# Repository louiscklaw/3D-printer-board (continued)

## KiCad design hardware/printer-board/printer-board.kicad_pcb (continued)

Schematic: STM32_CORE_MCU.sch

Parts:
C21, C23, C25, C26, C27, C28, C30, C31, C32: C104,0603; C_0603_1608Metric_Pad1.05x0.95mm_HandSolder
C22, C24: C10pf,0603; C_0603_1608Metric_Pad1.05x0.95mm_HandSolder
C29, C55: C105,0603; C_0603_1608Metric_Pad1.05x0.95mm_HandSolder
D17: PB9; LED_0603_1608Metric_Pad1.05x0.95mm_HandSolder
J28: SWD; PinHeader_1x04_P2.54mm_Vertical
J29: USB_DBG; PinHeader_1x05_P1.27mm_Vertical
J43: STM32_GTR; PinHeader_1x03_P1.27mm_Vertical
J44: SPI_DBG; PinHeader_1x04_P1.27mm_Vertical
JP6: BOOT0; SolderJumper-2_P1.3mm_Open_TrianglePad1.0x1.5mm
JP7: BOOT1; SolderJumper-2_P1.3mm_Open_TrianglePad1.0x1.5mm
JP10: RST; SW_SPST_CK_RS282G05A3
L1: L_2R2,1210; L_1210_3225Metric_Pad1.42x2.65mm_HandSolder
R3, R47: R220,0603; R_0603_1608Metric_Pad1.05x0.95mm_HandSolder
R40, R41: R472,0603; R_0603_1608Metric_Pad1.05x0.95mm_HandSolder
R42: R0,0603; C_0603_1608Metric_Pad1.05x0.95mm_HandSolder
R43: R0,0603; R_0603_1608Metric_Pad1.05x0.95mm_HandSolder
R44: R102,0603; R_0805_2012Metric_Pad1.15x1.40mm_HandSolder
R45, R46: R103,0603; R_0603_1608Metric_Pad1.05x0.95mm_HandSolder
R48: R152,0603; R_0603_1608Metric_Pad1.05x0.95mm_HandSolder
U8: STM32F407VET6; TQFP-100
Y1: O_8M,3225; OSC_3225

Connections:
/STM32_CORE/STM32_CORE_MCU/BOOT0: JP6.2, R46.1, U8.94 (BOOT0)
/STM32_CORE/STM32_CORE_MCU/BOOT1: JP7.2, R45.1, U8.37 (PB2/BOOT1)
/STM32_CORE/STM32_CORE_MCU/DM: R3.1, U8.70 (PA11/D-)
/STM32_CORE/STM32_CORE_MCU/DP: R47.1, R48.1, U8.71 (PA12/D+)
/STM32_CORE/STM32_CORE_MCU/GND-CAP1: C30.1, U8.49 (VSS_1/VCAP_1)
/STM32_CORE/STM32_CORE_MCU/GND-CAP2: C31.1, U8.73 (NC/VCAP_2)
/STM32_CORE/STM32_CORE_MCU/GND-VCC3V3: R42.1, R43.1, U8.19 (VSSA/VDD)
/STM32_CORE/STM32_CORE_MCU/MISO2: J44.2, U8.53 (PB14/MISO2)
/STM32_CORE/STM32_CORE_MCU/MOSI2: J44.1, U8.54 (PBI5/MOSI2)
/STM32_CORE/STM32_CORE_MCU/PB9: R44.1, U8.96 (PB9)
/STM32_CORE/STM32_CORE_MCU/RESET: C32.1, JP10.1 (A), U8.14 (NRST)
/STM32_CORE/STM32_CORE_MCU/SCK: J44.3, U8.52 (PB13/SCK2)
/STM32_CORE/STM32_CORE_MCU/SWCLK: J28.2, U8.76 (PA14/JTCK/SWCLK)
/STM32_CORE/STM32_CORE_MCU/SWDIO: J28.3, U8.72 (PA13/JTMS/SWDIO)
/STM32_CORE/STM32_SCL1: U8.92 (PB6/SCL1)
/STM32_CORE/STM32_SDA1: U8.93 (PB7/SDA1)
/orange_pi/OPI_USB-DM2: J29.2, R3.2; also elsewhere on the board
/orange_pi/OPI_USB-DP2: J29.3, R47.2; also elsewhere on the board
GND: C21.2, C22.2, C23.2, C24.2, C25.1, C26.1, C27.1, C28.1, C29.1, C30.2, C31.2, C32.2, C55.1, J28.1, J29.4, J29.5, J43.3, J44.4, JP10.2 (B), R43.2, R45.2, R46.2, U8.10 (VSS_5), U8.20 (VREF-), U8.27 (VSS_4), U8.74 (VSS_2), U8.99 (VSS_3), Y1.2; also elsewhere on the board
unnamed: C21.1, L1.2, U8.21 (VREF+)
unnamed: C22.1, U8.12 (OSC_IN), Y1.1
unnamed: C23.1, U8.6 (VBAT)
unnamed: C24.1, U8.13 (OSC_OUT), Y1.3
unnamed: D17.1 (K), R44.2
unnamed: J43.1, U8.69 (PA10/RX1)
unnamed: J43.2, U8.68 (PA9/TX1)
unnamed: JP6.1, R40.1
unnamed: JP7.1, R41.1
PA0: U8.23 (PA0/WKUP/ADC0); also elsewhere on the board
PA1: U8.24 (PA1/ADC1); also elsewhere on the board
PA2: U8.25 (PA2/ADC2/TX2); also elsewhere on the board
PA3: U8.26 (PA3/ADC3/RX2); also elsewhere on the board
PA4: U8.29 (PA4/ADC4/NSS1); also elsewhere on the board
PA6: U8.31 (PA6/ADC6/MISO1); also elsewhere on the board
PA7: U8.32 (PA7/ADC7/MOSI1); also elsewhere on the board
PA8: U8.67 (PA8/MCO); also elsewhere on the board
PA15: U8.77 (PA15/JTDI); also elsewhere on the board
PB5: U8.91 (PB5); also elsewhere on the board
PC0: U8.15 (PCO/ADC10); also elsewhere on the board
PC1: U8.16 (PC1/ADC11); also elsewhere on the board
PC2: U8.17 (PC2/ADC12); also elsewhere on the board
PC3: U8.18 (PC3/ADC13); also elsewhere on the board
PC4: U8.33 (PC4/ADC14); also elsewhere on the board
PC6: U8.63 (PC6); also elsewhere on the board
PC10: U8.78 (PC10); also elsewhere on the board
PC11: U8.79 (PC11); also elsewhere on the board
PC12: U8.80 (PC12); also elsewhere on the board
PC13: U8.7 (PC13/TAMP/RTC); also elsewhere on the board
PC14: U8.8 (PC14/OSCIN); also elsewhere on the board
PC15: U8.9 (PC15/OSCOUT); also elsewhere on the board
PD0: U8.81 (PD0); also elsewhere on the board
PD1: U8.82 (PD1); also elsewhere on the board
PD2: U8.83 (PD2); also elsewhere on the board
PD3: U8.84 (PD3); also elsewhere on the board
PD4: U8.85 (PD4); also elsewhere on the board
PD5: U8.86 (PD5); also elsewhere on the board
PD6: U8.87 (PD6); also elsewhere on the board
PD7: U8.88 (PD7); also elsewhere on the board
PD13: U8.60 (PD13); also elsewhere on the board
PD14: U8.61 (Pd14); also elsewhere on the board
PD15: U8.62 (PD15); also elsewhere on the board
PE2: U8.1 (PE2); also elsewhere on the board
PE3: U8.2 (PE3); also elsewhere on the board
PE4: U8.3 (PE4); also elsewhere on the board
PE7: U8.38 (PE7); also elsewhere on the board
PE8: U8.39 (PE8); also elsewhere on the board
PE9: U8.40 (PE9); also elsewhere on the board
PE10: U8.41 (PE10); also elsewhere on the board
PE11: U8.42 (PE11); also elsewhere on the board
PE12: U8.43 (PE12); also elsewhere on the board
PE13: U8.44 (PE13); also elsewhere on the board
PE14: U8.45 (PE14); also elsewhere on the board
PE15: U8.46 (PE15); also elsewhere on the board

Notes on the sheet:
When using USB, the PA11 (D-) and PA12 (D+) pins are reserved. The USB code assumes that PA12 (D+) has a fixed pullup resistor attached to it.
THIS IS OPTIONAL REFER TO OPi side
General considerations: The STM32 port currently requires an 8 MHz crystal for correct operation General considerations: When using serial, the UART used for communication with the host is fixed to pins PA9 (TX) and PA10 (RX). When using USB, the PA11 (D-) and PA12 (D+) pins are reserved. The USB c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

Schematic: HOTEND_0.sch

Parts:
D18: LED_RED,0603; LED_0603_1608Metric_Pad1.05x0.95mm_HandSolder
J31: HOT_END; mpt_0,5%2f2-2,54,heatbed
Q2: STP55NF06; TO-263-2,thermal_vias
R50: R100,0805; R_0805_2012Metric_Pad1.15x1.40mm_HandSolder
R51: R104,0805; R_0805_2012Metric_Pad1.15x1.40mm_HandSolder
R52: R182,0603; R_0603_1608Metric_Pad1.05x0.95mm_HandSolder

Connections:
+12V: J31.1, R52.2; also elsewhere on the board
/HOTENDS/HOTEND_0/-12V: D18.1 (K), J31.2, Q2.2 (D)
GND: Q2.3 (S), R51.1; also elsewhere on the board
unnamed: D18.2 (A), R52.1
unnamed: Q2.1 (G), R50.1
unnamed 152: R50.2, R51.2; also elsewhere on the board

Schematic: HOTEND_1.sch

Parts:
D19: LED_RED,0603; LED_0603_1608Metric_Pad1.05x0.95mm_HandSolder
J32: HOT_END; mpt_0,5%2f2-2,54,heatbed
Q3: STP55NF06; TO-263-2,thermal_vias
R53: R100,0805; R_0805_2012Metric_Pad1.15x1.40mm_HandSolder
R54: R104,0805; R_0805_2012Metric_Pad1.15x1.40mm_HandSolder
R55: R182,0603; R_0603_1608Metric_Pad1.05x0.95mm_HandSolder

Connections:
+12V: J32.1, R55.2; also elsewhere on the board
/HOTENDS/HOTEND_1/-12V: D19.1 (K), J32.2, Q3.2 (D)
GND: Q3.3 (S), R54.1; also elsewhere on the board
unnamed: D19.2 (A), R55.1
unnamed: Q3.1 (G), R53.1
unnamed 154: R53.2, R54.2; also elsewhere on the board

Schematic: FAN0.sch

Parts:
C36: CP1uf,50V; CP_Elec_4x5.3
D20: LED_BLUE,0603; LED_0603_1608Metric_Pad1.05x0.95mm_HandSolder
J33: TO FAN0; b2b-ph-kl,fan_pwm_out
Q4: D882; SOT-89-3,thermal_vias
R56: R100,0805; R_0805_2012Metric_Pad1.15x1.40mm_HandSolder
R57: R104,0805; R_0805_2012Metric_Pad1.15x1.40mm_HandSolder
R58: R100,0603; R_0603_1608Metric_Pad1.05x0.95mm_HandSolder
R59: R182,0603; R_0603_1608Metric_Pad1.05x0.95mm_HandSolder

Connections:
+12V: C36.1, J33.1, R59.2; also elsewhere on the board
/FANS/FAN0/FAN0_N: C36.2, D20.1 (K), J33.2, R58.1
GND: Q4.3 (E), R57.1; also elsewhere on the board
unnamed: D20.2 (A), R59.1
unnamed: Q4.1 (B), R56.1
unnamed: Q4.2 (C), R58.2
PA6: R56.2, R57.2; also elsewhere on the board

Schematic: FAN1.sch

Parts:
C37: CP1uf,50V; CP_Elec_4x5.3
D21: LED_BLUE,0603; LED_0603_1608Metric_Pad1.05x0.95mm_HandSolder
J34: TO FAN1; b2b-ph-kl,fan_pwm_out
Q5: D882; SOT-89-3,thermal_vias
R60: R100,0805; R_0805_2012Metric_Pad1.15x1.40mm_HandSolder
R61: R104,0805; R_0805_2012Metric_Pad1.15x1.40mm_HandSolder
R62: R100,0603; R_0603_1608Metric_Pad1.05x0.95mm_HandSolder
R63: R182,0603; R_0603_1608Metric_Pad1.05x0.95mm_HandSolder

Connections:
+12V: C37.1, J34.1, R63.2; also elsewhere on the board
/FANS/FAN1/FAN1_N: C37.2, D21.1 (K), J34.2, R62.1
GND: Q5.3 (E), R61.1; also elsewhere on the board
unnamed: D21.2 (A), R63.1
unnamed: Q5.1 (B), R60.1
unnamed: Q5.2 (C), R62.2
PA7: R60.2, R61.2; also elsewhere on the board

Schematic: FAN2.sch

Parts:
C38: CP1uf,50V; CP_Elec_4x5.3
D22: LED_BLUE,0603; LED_0603_1608Metric_Pad1.05x0.95mm_HandSolder
J35: TO FAN2; b2b-ph-kl,fan_pwm_out
Q6: D882; SOT-89-3,thermal_vias
R64: R100,0805; R_0603_1608Metric_Pad1.05x0.95mm_HandSolder
R65: R104,0805; R_0805_2012Metric_Pad1.15x1.40mm_HandSolder
R66: R100,0603; R_0603_1608Metric_Pad1.05x0.95mm_HandSolder
R67: R182,0603; R_0603_1608Metric_Pad1.05x0.95mm_HandSolder

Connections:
+12V: C38.1, J35.1, R67.2; also elsewhere on the board
/FANS/FAN2/FAN2_N: C38.2, D22.1 (K), J35.2, R66.1
GND: Q6.3 (E), R65.1; also elsewhere on the board
unnamed: D22.2 (A), R67.1
unnamed: Q6.1 (B), R64.1
unnamed: Q6.2 (C), R66.2
PA8: R64.2, R65.2; also elsewhere on the board

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
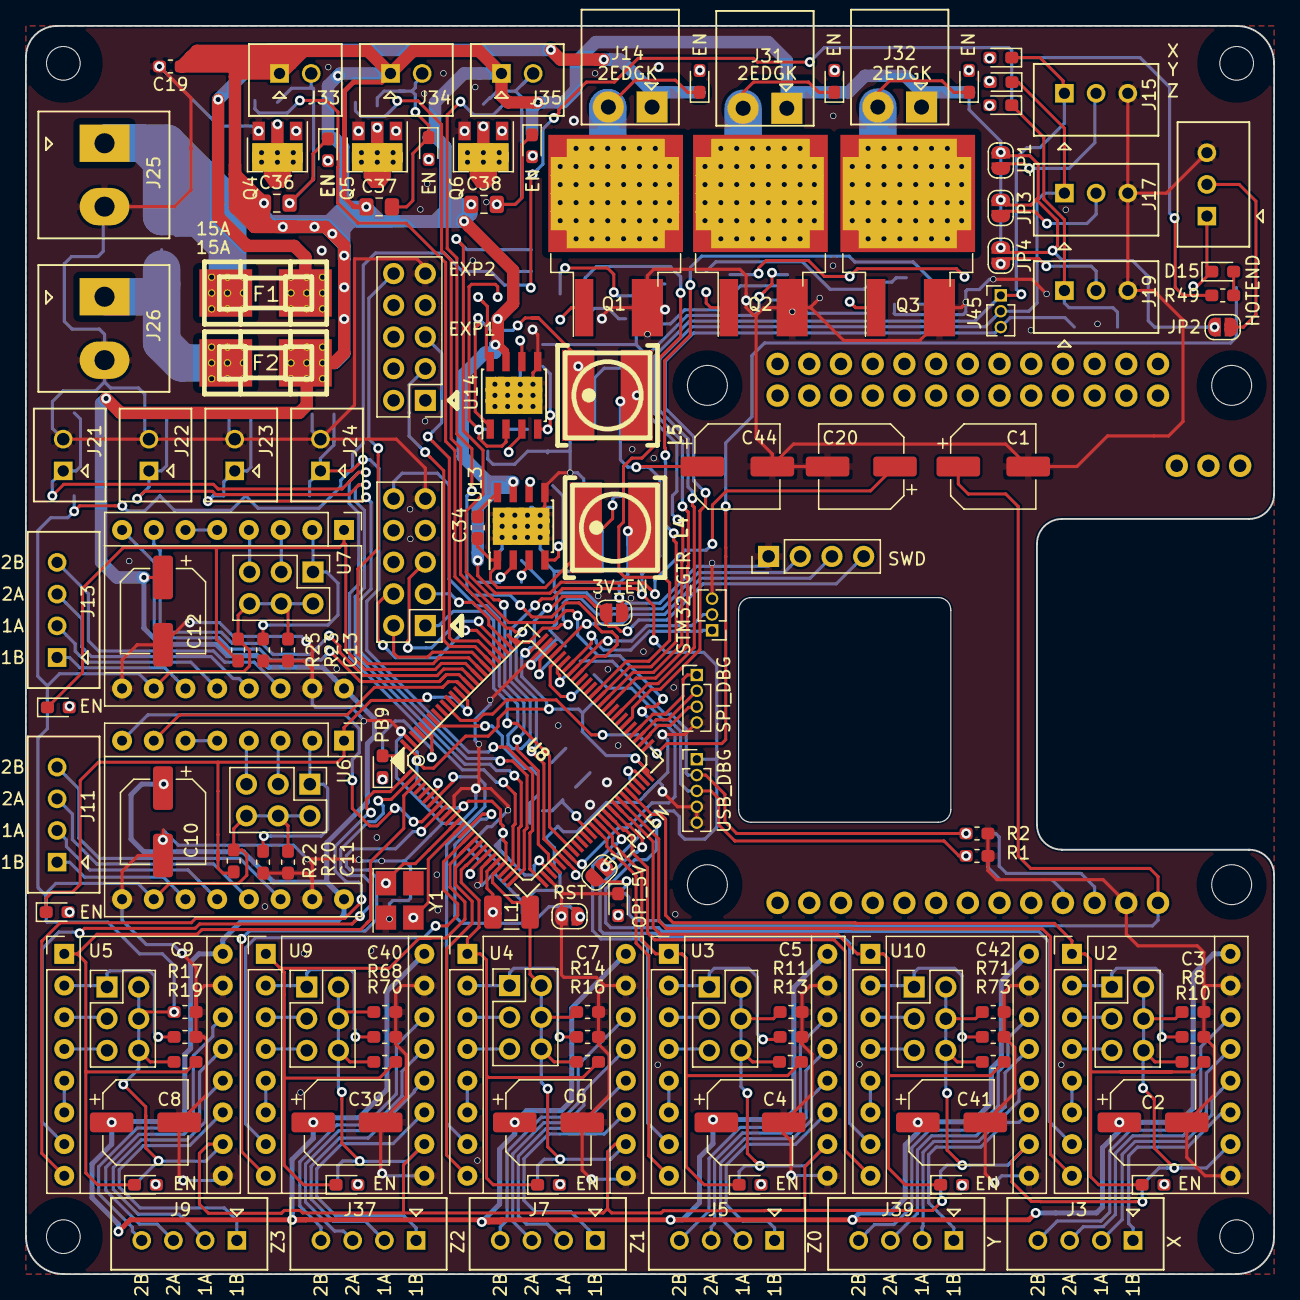
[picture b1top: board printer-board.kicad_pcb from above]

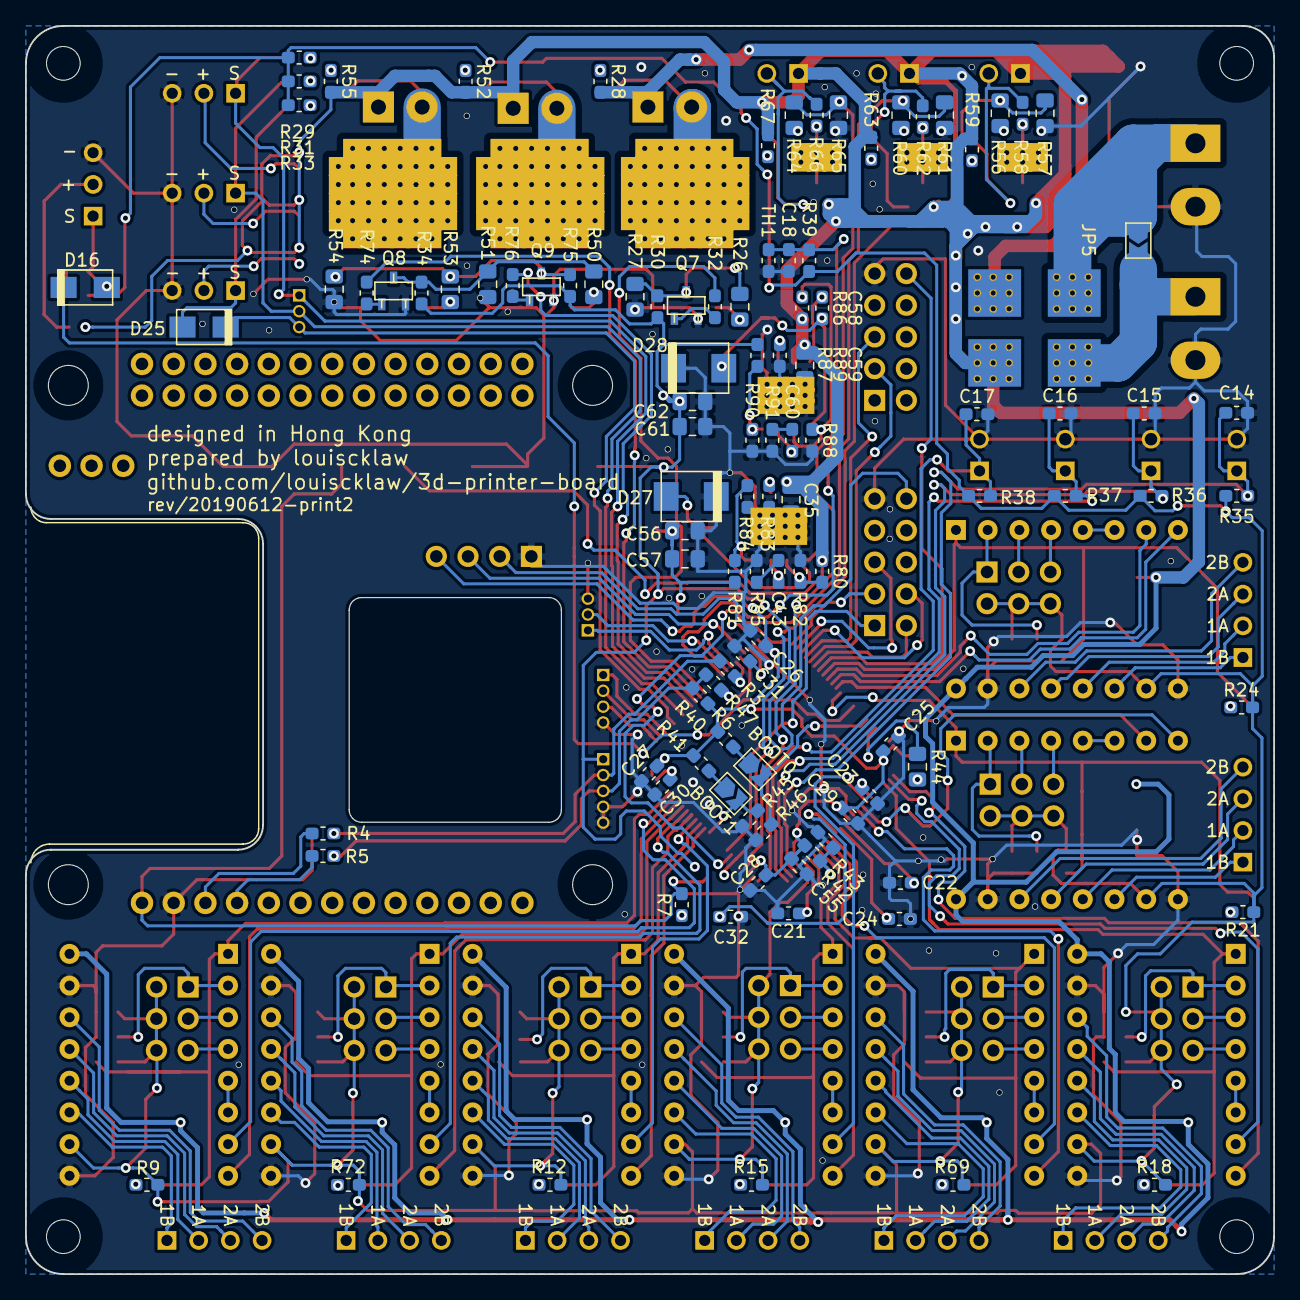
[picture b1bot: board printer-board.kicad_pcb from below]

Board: 2 copper layers, 100.0 x 100.0 mm, 243 parts (107 on the bottom side), 207 nets.

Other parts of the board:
C58: C104,0603; C_0603_1608Metric_Pad1.05x0.95mm_HandSolder
C59, C61, C62: C106,0805; C_0805_2012Metric_Pad1.15x1.40mm_HandSolder
C60: C151,0603; C_0603_1608Metric_Pad1.05x0.95mm_HandSolder
D28: SD_1N5822_SS34; do214aa
JP3, JP4: 12V_EN; SolderJumper-2_P1.3mm_Open_RoundedPad1.0x1.5mm
L5: L_15uH; inductor_smd_6.8x3.8mm
Q7, Q8, Q9: SS9013_J3; 9013,J3,SOT23
R74, R76: R471,0603; R_0603_1608Metric_Pad1.05x0.95mm_HandSolder
R75: R331,0603; R_0603_1608Metric_Pad1.05x0.95mm_HandSolder
R86, R89, R91: R104,0603; R_0603_1608Metric_Pad1.05x0.95mm_HandSolder
R87: R224,0603; R_0603_1608Metric_Pad1.05x0.95mm_HandSolder
R88: R240,0603; R_0603_1608Metric_Pad1.05x0.95mm_HandSolder
R90: R433,0603; R_0603_1608Metric_Pad1.05x0.95mm_HandSolder
U14: MP1584; MP1584,SOIC-8_3.9x4.9mm_P1.27mm,thermal_via

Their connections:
+12V: C59.1, JP3.1, JP4.1, R86.1, U14.7; also elsewhere on the board
GND: C59.2, C61.2, C62.2, D28.2, Q7.2, Q8.2, Q9.2, R88.2, R89.2, R90.2, R91.2, U14.5, U14.G; also elsewhere on the board
unnamed: C58.1, D28.1, L5.1, U14.1
unnamed: C58.2, U14.8
unnamed: C60.1, U14.3
unnamed: C60.2, R91.1
unnamed 150: Q7.3; also elsewhere on the board
unnamed: Q8.1, R74.1
unnamed 152: Q8.3; also elsewhere on the board
unnamed: Q9.1, R76.1
unnamed 154: Q9.3, R75.2; also elsewhere on the board
unnamed: R86.2, R88.1, U14.2
unnamed: R87.2, R90.1, U14.4
unnamed: R89.1, U14.6
PD14: R76.2; also elsewhere on the board
PD15: R74.2; also elsewhere on the board

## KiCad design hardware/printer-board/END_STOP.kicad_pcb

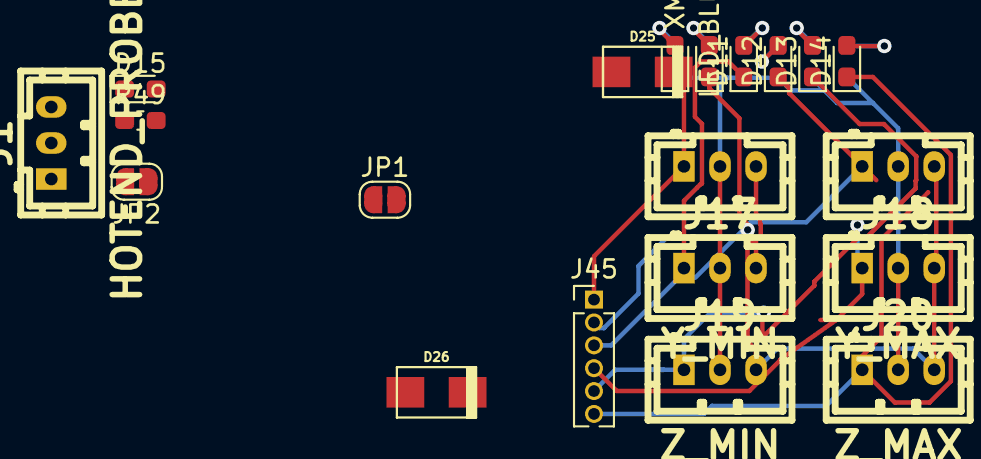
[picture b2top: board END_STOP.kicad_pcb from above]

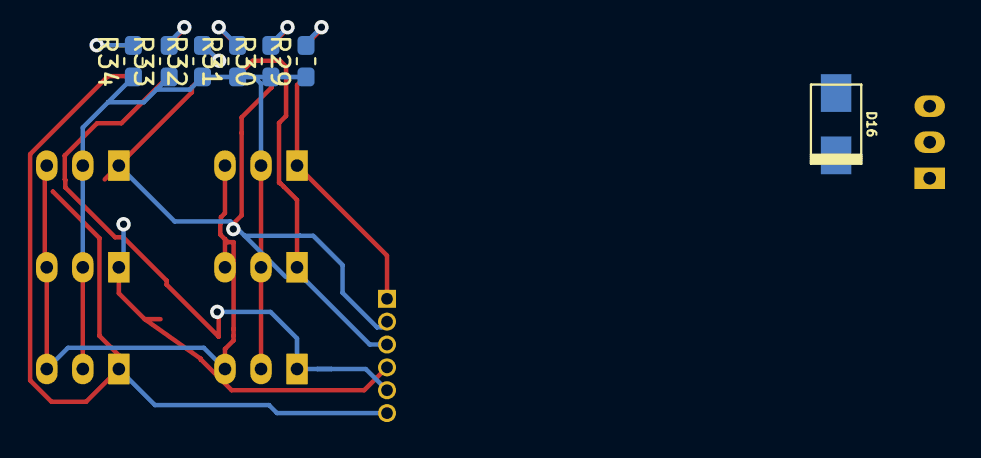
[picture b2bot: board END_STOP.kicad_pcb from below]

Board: 2 copper layers, 27 parts (7 on the bottom side), 21 nets.

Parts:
D9: XMIN; LED_0603_1608Metric_Pad1.05x0.95mm_HandSolder
D10, D11, D12, D13, D14, D15: LED_BLUE,0603; LED_0603_1608Metric_Pad1.05x0.95mm_HandSolder
D16, D25, D26: SD_1N5817_SS12; do214ac
J1: HOTEND_PROBE; b3b-ph-kl,end_stop
J15: X_MIN; b3b-ph-kl,end_stop
J16: X_MAX; b3b-ph-kl,end_stop
J17: Y_MIN; b3b-ph-kl,end_stop
J18: Y_MAX; b3b-ph-kl,end_stop
J19: Z_MIN; b3b-ph-kl,end_stop
J20: Z_MAX; b3b-ph-kl,end_stop
J45: END_SWITCH_DEBUG; PinHeader_1x06_P1.27mm_Vertical
JP1, JP2: SolderJumper_2_Open; SolderJumper-2_P1.3mm_Open_RoundedPad1.0x1.5mm
R29, R30, R31, R32, R33, R34, R49: R102,0603; R_0603_1608Metric_Pad1.05x0.95mm_HandSolder

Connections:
+3V3_STM32: R29.1, R30.1, R31.1, R32.1, R33.1, R34.1, R49.1
+12V: JP1.1, JP2.1
/X_MAX: D10.1, J16.1, J45.2
/X_MIN: D9.1, J15.1, J45.1
/Y_MAX: D12.1, J18.1, J45.4
/Y_MIN: D11.1, J17.1, J45.3
/Z_MAX: D26.2, J45.6
/Z_MIN: D25.2, J45.5
GND: J1.3, J15.3, J16.3, J17.3, J18.3, J19.3, J20.3
unnamed: D9.2, R29.2
unnamed: D10.2, R30.2
unnamed: D11.2, R31.2
unnamed: D12.2, R32.2
unnamed: D13.1, D25.1, J19.1
unnamed: D13.2, R33.2
unnamed: D14.1, D26.1, J20.1
unnamed: D14.2, R34.2
unnamed: D15.1, D16.1, J1.1
unnamed: D15.2, R49.2
unnamed: J1.2, JP2.2
unnamed: J15.2, J16.2, J17.2, J18.2, J19.2, J20.2, JP1.2

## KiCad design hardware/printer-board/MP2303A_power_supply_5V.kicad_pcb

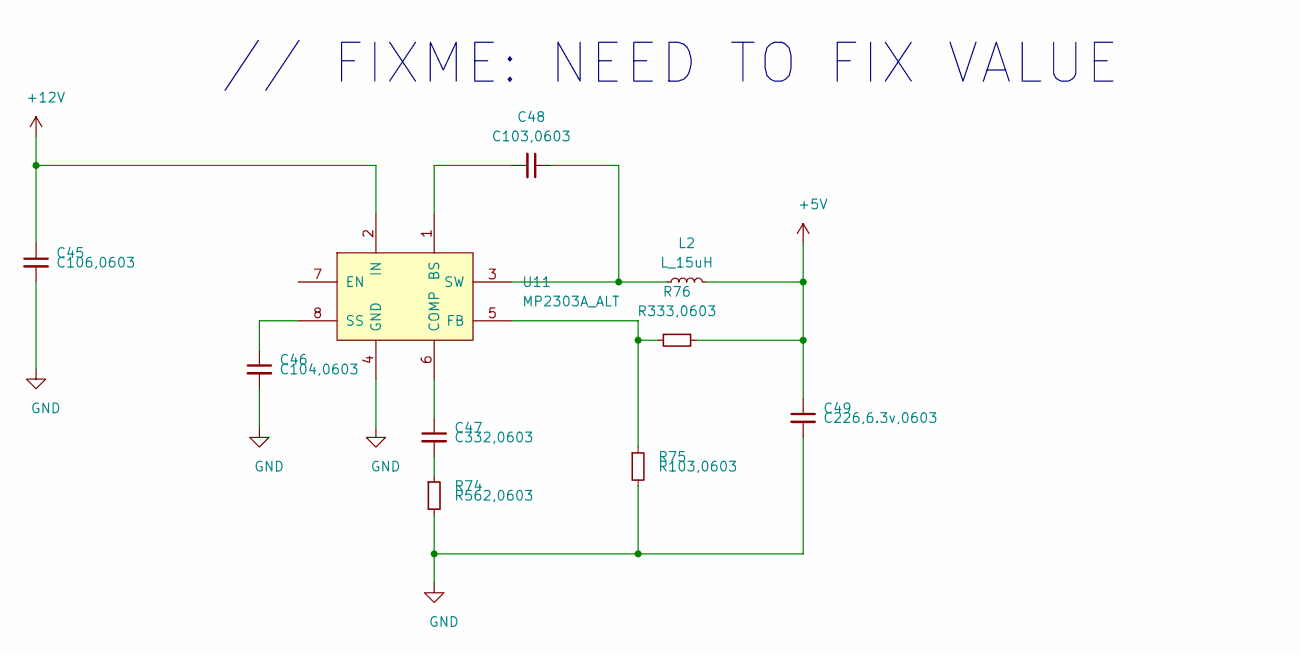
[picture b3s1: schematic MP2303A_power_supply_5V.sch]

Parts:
C45: C106,0603; C_0603_1608Metric_Pad1.05x0.95mm_HandSolder
C46: C104,0603; C_0603_1608Metric_Pad1.05x0.95mm_HandSolder
C47: C332,0603; C_0603_1608Metric_Pad1.05x0.95mm_HandSolder
C48: C103,0603; C_0603_1608Metric_Pad1.05x0.95mm_HandSolder
C49: C226,6.3v,0603; C_0603_1608Metric_Pad1.05x0.95mm_HandSolder
L2: L_15uH; inductor_smd_4.8x2.8mm
R74: R562,0603; R_0603_1608Metric_Pad1.05x0.95mm_HandSolder
R75: R103,0603; R_0603_1608Metric_Pad1.05x0.95mm_HandSolder
R76: R333,0603; R_0603_1608Metric_Pad1.05x0.95mm_HandSolder
U11: MP2303A_ALT; SOIC-8_3.9x4.9mm_P1.27mm,thermal_via

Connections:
+5V: C49.1, L2.2, R76.1
+12V: C45.1, U11.2 (IN)
GND: C45.2, C46.2, C49.2, R74.2, R75.2, U11.4 (GND)
unnamed: C46.1, U11.8 (SS)
unnamed: C47.1, U11.6 (COMP)
unnamed: C47.2, R74.1
unnamed: C48.1, L2.1, U11.3 (SW)
unnamed: C48.2, U11.1 (BS)
unnamed: R75.1, R76.2, U11.5 (FB)

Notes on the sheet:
// FIXME: NEED TO FIX VALUE

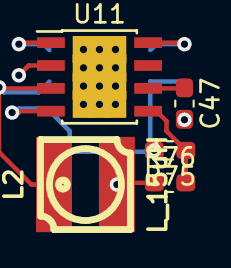
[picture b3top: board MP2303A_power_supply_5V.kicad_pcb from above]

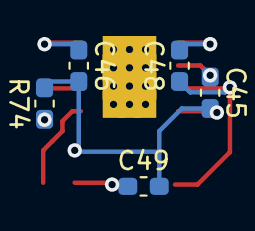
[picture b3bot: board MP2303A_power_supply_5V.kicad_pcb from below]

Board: 2 copper layers, 10 parts (5 on the bottom side), 9 nets.

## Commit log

2019-04-01 update,
2019-04-26 update to add indicator for end-stop,
2019-04-26 update design goal,
2019-04-27 update for endstop circuit,
2019-04-27 update to reverse NO/NC,
2019-04-27 update for stepper motor circuit,
2019-04-27 update to remove E3,
2019-04-27 udpate design goal,
2019-04-27 update label,
2019-04-27 update power supply circuit,
2019-04-27 update hotend MOSFET,
2019-04-27 update power tree,
2019-04-27 need to verify i2c circuit,
2019-04-27 update stm32-core,
2019-04-27 update annotations,
2019-04-27 update power circuit,
2019-04-28 update heater layouts,
2019-04-28 update hotend pcb,
2019-04-28 update hotend,
2019-04-28 update heatbed,
2019-04-29 update for usb pull up resistor,
2019-04-30 update RAMPS 1.7,
2019-04-30 update power,
2019-04-30 udpate,
2019-04-30 update for fans,
2019-04-30 update for power circuits,
2019-05-01 fix min/max stop footprint,
2019-05-01 fix termistor cap footprint,
2019-05-01 remove jumper in display FPC,
2019-05-01 update to re-annotation,
2019-05-01 update for stepper Z,
2019-05-01 update hotend footprint,
2019-05-01 routing,
2019-05-02 update positino,
2019-05-02 fix 3v3 and 5v connected,
2019-05-02 remove unnecessary capacitor,
2019-05-02 update step motor terminal orientation,
2019-05-02 update driver position,
2019-05-02 update driver positin,
2019-05-02 update ROUTING,
2019-05-05 add renders image,
2019-05-05 update README.md,
2019-05-05 update TEAR DROP,
2019-05-06 update for stepper labelling,
2019-05-06 update copper clearance area for mount holes,
2019-05-07 update datasheet,
2019-05-12 update README,
2019-05-12 update for documentation,
2019-05-12 update fabfile,
2019-05-12 update working README.md generator,
2019-05-13 test resize pcb img.
2019-05-13 update README pcb image,
2019-05-13 relocate pdf files,
2019-05-15 update for photo in 5v schematic,
2019-05-16 fix footprint, in the middle,
2019-05-16 update R75, R76 labelling,
2019-05-16 update fixme,
2019-05-16 update MP2303,
2019-05-17 in the middle,
2019-05-17 init 3v3 sheet,
2019-05-17 update to ignore bak file,
2019-05-17 update annotation,
2019-05-17 update to remove old MP2303 circuit,
2019-05-17 update footprint,
2019-05-17 updaste to remote bak file,
2019-05-17 before remove MP2303,
2019-05-18 update point-schedule,
2019-05-19 update to add optional text only,
2019-05-19 update build script,
2019-05-19 update taobao part list,
2019-05-19 update point schedule for TRACESWO,
2019-05-19 update to ignore .vscode,
2019-05-21 update for orange pi terminals,
2019-05-21 update todo on next rev,
2019-05-21 update todo,
2019-05-21 update configuration file,
2019-05-21 update stepper config,
2019-05-21 update point schedule,
2019-05-21 update printer.cfg,
2019-05-21 update inductor footprint,
2019-05-21 update footprint of L1,
2019-05-21 update for heatsink footprint,
2019-06-11 working for stepper motor x,
2019-06-12 fix fan terminals,
2019-06-12 update for E0 en pin,
2019-06-12 update stepper motor terminal size,
2019-06-12 update for DRC,
2019-06-12 update for adding en jumper,
2019-06-12 update for routing,
2019-06-13 break board outline and perform autoroute,
2019-06-15 update,.
2019-06-15 fix beeper PC3,
2019-09-26 update for manual,
2020-02-04 update for adding photo,
2020-05-05 ci: init travis token,
2020-05-05 ci: init travis build config,
2020-05-06 fix: remove missing submodule,
2020-05-06 fixing submodule url path,
